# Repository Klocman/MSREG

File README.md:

## MSREG (Most recently MSREG33E)
Temperature and (optionally) humidity regulator based on DS18B20 or DHT22 sensors. This project contains the board layout, firmware, bootloader, and Windows tools that can be used with the regulator to monitor, configure, and update it. 

This regulator can be used for terrariums, heaters, egg incubators, refrigerators - anything that depends on stable temperature and/or humidity, and can be controlled by turning something On or Off.

## Features and technical specifications
[Read the datasheet (only in Polish at the moment)](https://github.com/Klocman/MSREG/blob/master/Documentation/datasheet_pl_msreg33E_r7.pdf)

## Compiling / Software required
Boards and schematics were created with Eagle PCB v6.6.0. 

Firmare and Bootloader can be opened and compiled with Atmel Studio 6 or newer. The bootloader .hex has to be manually merged with the main firmware .hex.

The Windows applications can be compiled in any modern version of Visual Studio with C# support.

## Photos and videos of the regulator
[Youtube video of MSREG33E working with the Windows application](https://youtu.be/d277WWdbOqA?t=52s)

[You can view the full gallery here](https://github.com/Klocman/MSREG/tree/master/Documentation/Photos)

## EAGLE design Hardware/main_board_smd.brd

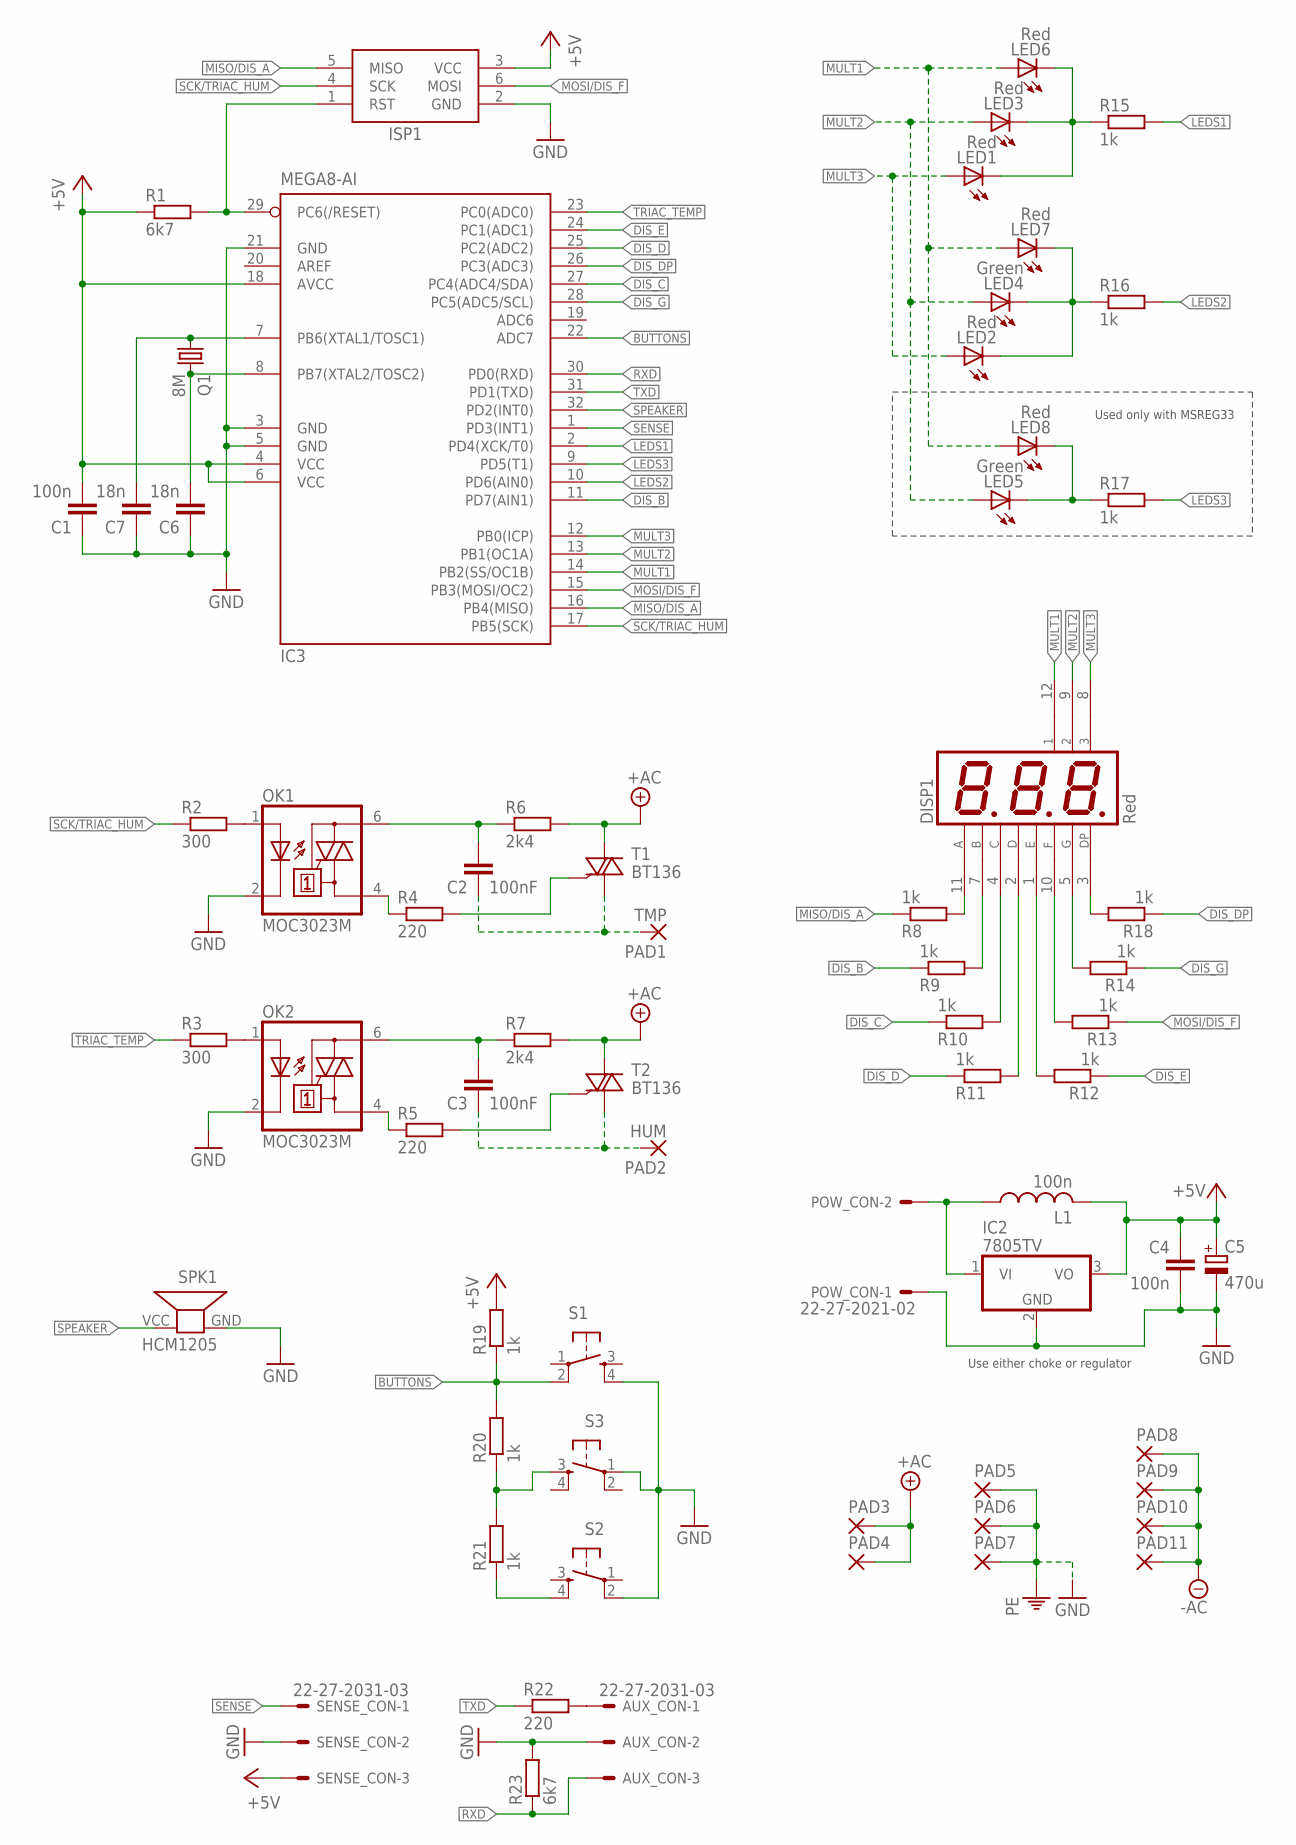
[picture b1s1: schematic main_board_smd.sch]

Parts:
AUX_CON: 22-27-2031-03; 6410-03
C1: 100n; C2.5-4
C2, C3: 100nF; C102-054X133
C4: 100n; C2.5-2
C5: 470u; TT2D7
C6, C7: 18n; C2.5-2
DISP1: Red; 7SEG3DIG
IC2: 7805TV; TO220V
IC3: MEGA8-AI; TQFP32-08
ISP1: AVRISPAV; AVRISP-KLOC
L1: 100n; 0204/7
LED1, LED2, LED3, LED6, LED7, LED8: Red; LED5MM
LED4, LED5: Green; LED5MM
OK1, OK2: MOC3023M; DIL06
PAD1: TMP; KLOCWIRE
PAD2: HUM; KLOCWIRE
PAD3, PAD4, PAD5, PAD6, PAD7, PAD8, PAD9, PAD10, PAD11: 3,17/1,3KLOC; KLOCWIRE
POW_CON: 22-27-2021-02; 6410-02
Q1: 8M; HC49U-V
R1: 6k7; 0204/5
R2, R3: 300; 0204/7
R4, R22: 220; 0204/7
R5: 220; 0207/10
R6: 2k4; 0411V
R7: 2k4; 0411/12
R8, R9, R10, R11, R12, R13, R14, R18: 1k; 0204V
R15, R16, R19, R20, R21: 1k; 0204/5
R17: 1k; 0204/7
R23: 6k7; 0204/7
S1, S2, S3: TAC_SWITCHPTH; TACTILE-PTH
SENSE_CON: 22-27-2031-03; 6410-03
SPK1: HCM1205; HCM12XX
T1, T2: BT136; TRIAC_VE

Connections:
+5V: C1.2, C4.1, C5.+, IC2.3 (VO), IC3.4 (VCC), IC3.6 (VCC), IC3.18 (AVCC), ISP1.3 (VCC), L1.2, R1.1, R19.2, SENSE_CON.3
+UB: PAD3.1, PAD4.1, R6.2, R7.2, T1.A (A2), T2.A (A2)
-UB: PAD8.1, PAD9.1, PAD10.1, PAD11.1
BUTTONS: IC3.22 (ADC7), R19.1, R20.2, S1.2
DIS_B: IC3.11 (PD7(AIN1)), R9.1
DIS_C: IC3.27 (PC4(ADC4/SDA)), R10.1
DIS_D: IC3.25 (PC2(ADC2)), R11.1
DIS_DP: IC3.26 (PC3(ADC3)), R18.1
DIS_E: IC3.24 (PC1(ADC1)), R12.1
DIS_G: IC3.28 (PC5(ADC5/SCL)), R14.1
GND: AUX_CON.2, C1.1, C4.2, C5.-, C6.1, C7.1, IC2.2 (GND), IC3.3 (GND), IC3.5 (GND), IC3.21 (GND), ISP1.2 (GND), OK1.2 (C), OK2.2 (C), PAD5.1, PAD6.1, PAD7.1, POW_CON.1, R23.2, S1.4, S2.2, S3.1, SENSE_CON.2, SPK1.GND
LEDS1: IC3.2 (PD4(XCK/T0)), R15.2
LEDS2: IC3.10 (PD6(AIN0)), R16.2
LEDS3: IC3.9 (PD5(T1)), R17.2
MISO/DIS_A: IC3.16 (PB4(MISO)), ISP1.5 (MISO), R8.1
MOSI/DIS_F: IC3.15 (PB3(MOSI/OC2)), ISP1.6 (MOSI), R13.1
MULT1: DISP1.12 (1), IC3.14 (PB2(SS/OC1B)), LED6.A, LED7.A, LED8.A
MULT2: DISP1.9 (2), IC3.13 (PB1(OC1A)), LED3.A, LED4.A, LED5.A
MULT3: DISP1.8 (3), IC3.12 (PB0(ICP)), LED1.A, LED2.A
unnamed: DISP1.3 (DP), R18.2
unnamed: DISP1.2 (D), R11.2
unnamed: DISP1.4 (C), R10.2
unnamed: DISP1.7 (B), R9.2
unnamed: DISP1.11 (A), R8.2
unnamed: DISP1.1 (E), R12.2
unnamed: DISP1.10 (F), R13.2
unnamed: DISP1.5 (G), R14.2
unnamed: C7.2, IC3.7 (PB6(XTAL1/TOSC1)), Q1.1
unnamed: C6.2, IC3.8 (PB7(XTAL2/TOSC2)), Q1.2
unnamed: LED1.K (C), LED3.K (C), LED6.K (C), R15.1
unnamed: LED5.K (C), LED8.K (C), R17.1
unnamed: IC2.1 (VI), L1.1, POW_CON.2
unnamed: LED2.K (C), LED4.K (C), LED7.K (C), R16.1
unnamed: C2.1, OK1.6 (A2), R6.1
unnamed: C2.2, PAD1.1, T1.C (A1)
unnamed: OK2.1 (A), R3.2
unnamed: OK2.4 (A1), R5.1
unnamed: R5.2, T2.G
unnamed: OK1.4 (A1), R4.1
unnamed: C3.1, OK2.6 (A2), R7.1
unnamed: C3.2, PAD2.1, T2.C (A1)
unnamed: AUX_CON.1, R22.2
unnamed: R4.2, T1.G
unnamed: R20.1, R21.2, S3.3
unnamed: R21.1, S2.4
unnamed: OK1.1 (A), R2.2
RESET: IC3.29 (PC6(/RESET)), ISP1.1 (RST), R1.2
RXD: AUX_CON.3, IC3.30 (PD0(RXD)), R23.1
SCK/TRIAC_HUM: IC3.17 (PB5(SCK)), ISP1.4 (SCK), R2.1
SENSE: IC3.1 (PD3(INT1)), SENSE_CON.1
SPEAKER: IC3.32 (PD2(INT0)), SPK1.VCC
TRIAC_TEMP: IC3.23 (PC0(ADC0)), R3.1
TXD: IC3.31 (PD1(TXD)), R22.1

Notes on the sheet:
Use either choke or regulator
Used only with MSREG33

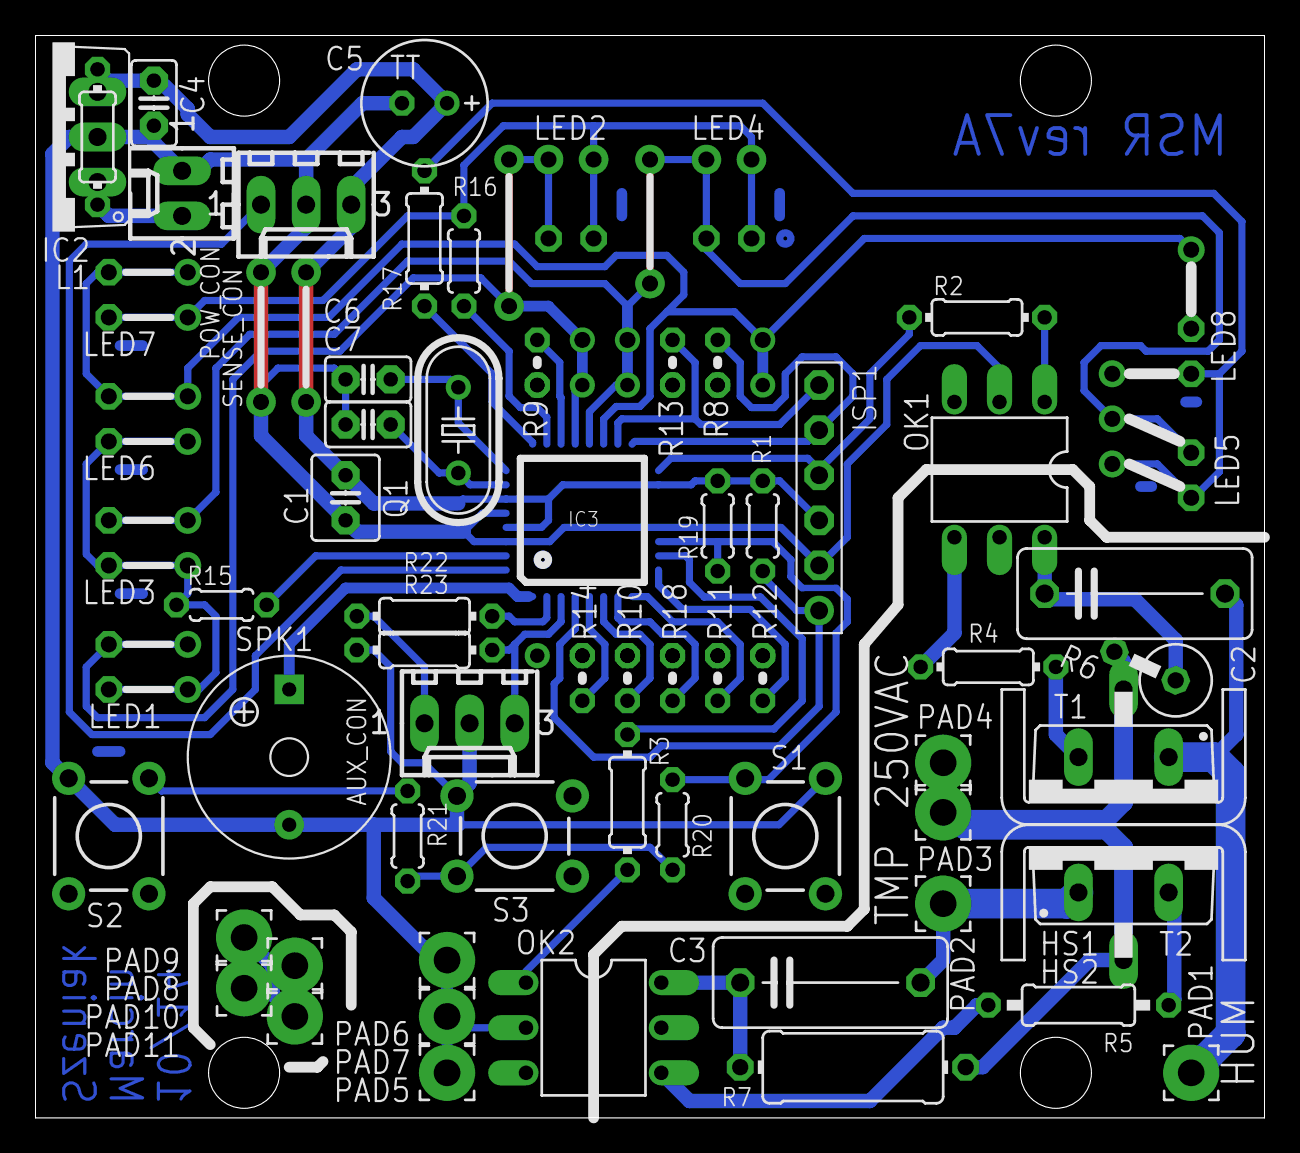
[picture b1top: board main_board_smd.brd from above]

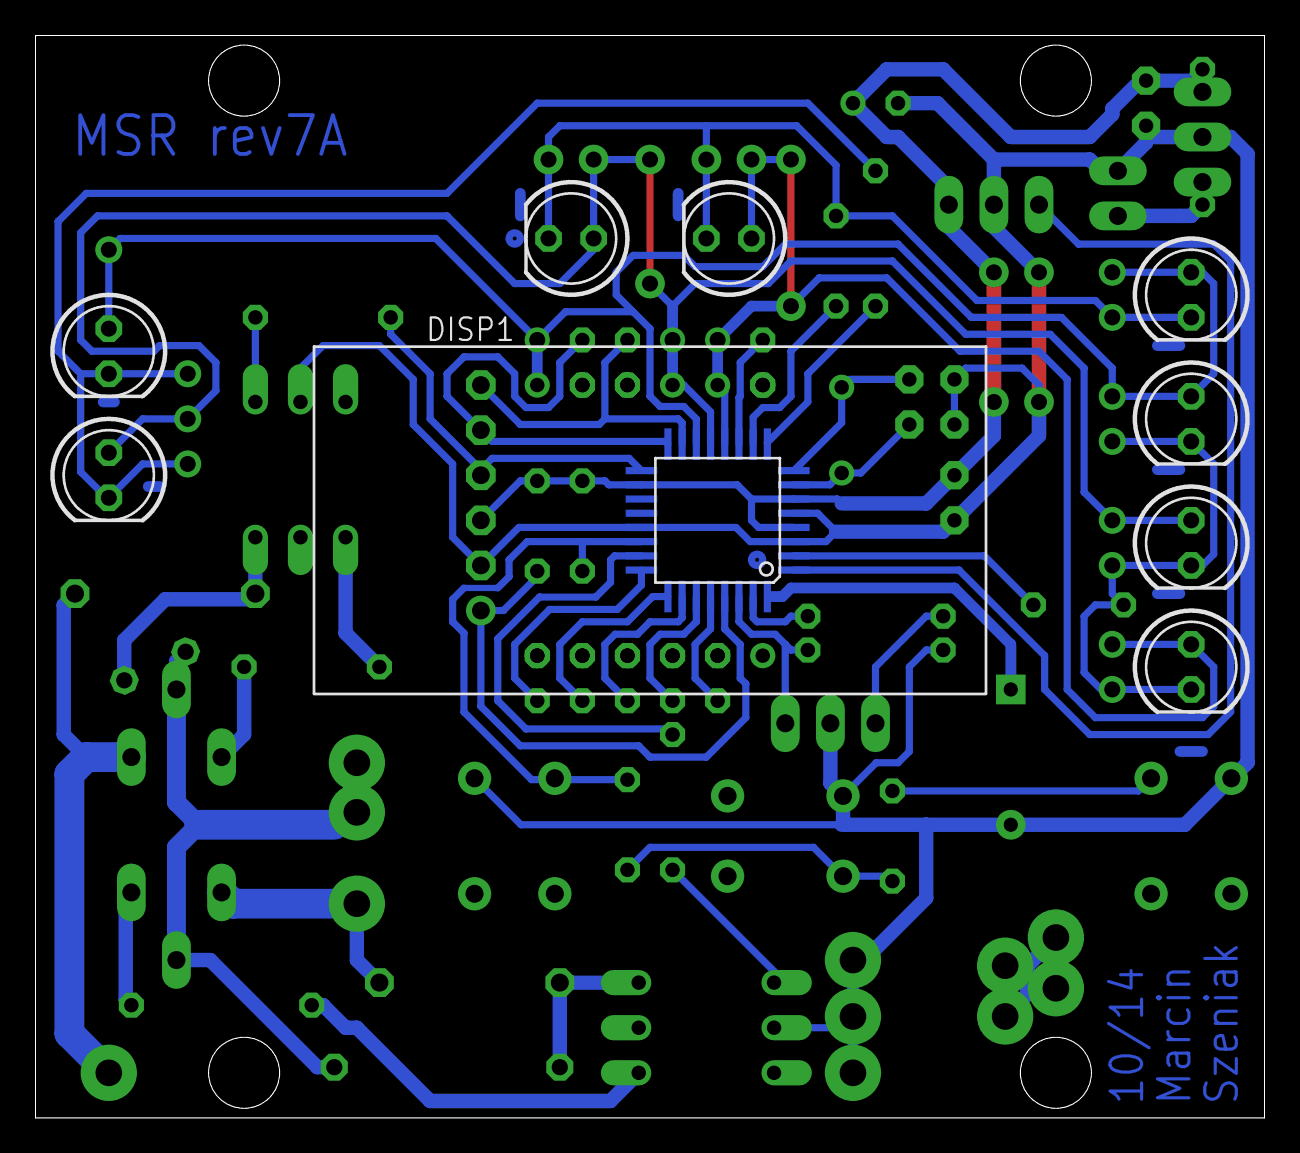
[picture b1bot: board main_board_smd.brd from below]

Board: 2 copper layers, 69.2 x 61.0 mm, 68 parts (10 on the bottom side), 53 nets.

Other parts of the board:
HS1, HS2: D03S

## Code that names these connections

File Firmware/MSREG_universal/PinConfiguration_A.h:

/*
 * PinConfiguration.h
 *
 * Created: 20-09-14 2:21:55 PM
 *  Author: Klocman
 */ 


#ifndef PINCONFIGURATION_H_
#define PINCONFIGURATION_H_

#define SEVSEG_A_PIN PINB4
#define SEVSEG_A_PORT PORTB
#define SEVSEG_A_DDR DDRB
#define SEVSEG_B_PIN PIND7
#define SEVSEG_B_PORT PORTD
#define SEVSEG_B_DDR DDRD
#define SEVSEG_C_PIN PINC4
#define SEVSEG_C_PORT PORTC
#define SEVSEG_C_DDR DDRC
#define SEVSEG_D_PIN PINC2
#define SEVSEG_D_PORT PORTC
#define SEVSEG_D_DDR DDRC
#define SEVSEG_E_PIN PINC1
#define SEVSEG_E_PORT PORTC
#define SEVSEG_E_DDR DDRC
#define SEVSEG_F_PIN PINB3
#define SEVSEG_F_PORT PORTB
#define SEVSEG_F_DDR DDRB
#define SEVSEG_G_PIN PINC5
#define SEVSEG_G_PORT PORTC
#define SEVSEG_G_DDR DDRC
#define SEVSEG_DP_PIN PINC3
#define SEVSEG_DP_PORT PORTC
#define SEVSEG_DP_DDR DDRC

#define MULTIPLEX_1_PIN PINB2
#define MULTIPLEX_2_PIN PINB1
#define MULTIPLEX_3_PIN PINB0
#define MULTIPLEX_1_DDR DDRB
#define MULTIPLEX_2_DDR DDRB
#define MULTIPLEX_3_DDR DDRB
#define MULTIPLEX_1_PORT PORTB
#define MULTIPLEX_2_PORT PORTB
#define MULTIPLEX_3_PORT PORTB

#define BUTTON_ADC 7

#define SENSOR_PIN PIND3
#define SENSOR_DDR DDRD
#define SENSOR_PORT PORTD
#define SENSOR_PORT_IN PIND

#define SPEAKER_PIN PIND2
#define SPEAKER_DDR DDRD
#define SPEAKER_PORT PORTD

#define TRIAC_HUM_PIN PINB5
#define TRIAC_HUM_DDR DDRB
#define TRIAC_HUM_PORT PORTB
#define TRIAC_TEMP_PORT PORTC
#define TRIAC_TEMP_DDR DDRC
#define TRIAC_TEMP_PIN PINC0

#define LEDS_1_PIN PIND4
#define LEDS_2_PIN PIND6
#define LEDS_3_PIN PIND5
#define LEDS_1_DDR DDRD
#define LEDS_2_DDR DDRD
#define LEDS_3_DDR DDRD
#define LEDS_1_PORT PORTD
#define LEDS_2_PORT PORTD
#define LEDS_3_PORT PORTD

#define OUTPUT_TRANSMIT_PIN PIND1
#define OUTPUT_TRANSMIT_DDR DDRD
#define OUTPUT_RECEIVE_PIN PIND0
#define OUTPUT_RECEIVE_DDR DDRD
#define OUTPUT_RECEIVE_PORT PORTD


#endif /* PINCONFIGURATION_H_ */

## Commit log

2015-09-30 Test commit
2016-10-09 Migrated project to Git
2016-10-09 Added sensor connection information
2016-10-09 Added premade datasheet
2016-10-09 Added the case stickers
2016-10-09 Uploaded a fixed version of the sticker
2016-10-10 Added photos of the finished, working device
2016-10-10 Added a photo of a fully assembled regulator with its back removed

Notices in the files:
parts and their libraries:
SparkFun-Electromechanical: Licensing: CC v3.0 Share-Alike You are welcome to use this library for commercial purposes.
